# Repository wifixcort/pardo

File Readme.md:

Pardo Board

M0 personaliced. Based on Adafruit Feather M0

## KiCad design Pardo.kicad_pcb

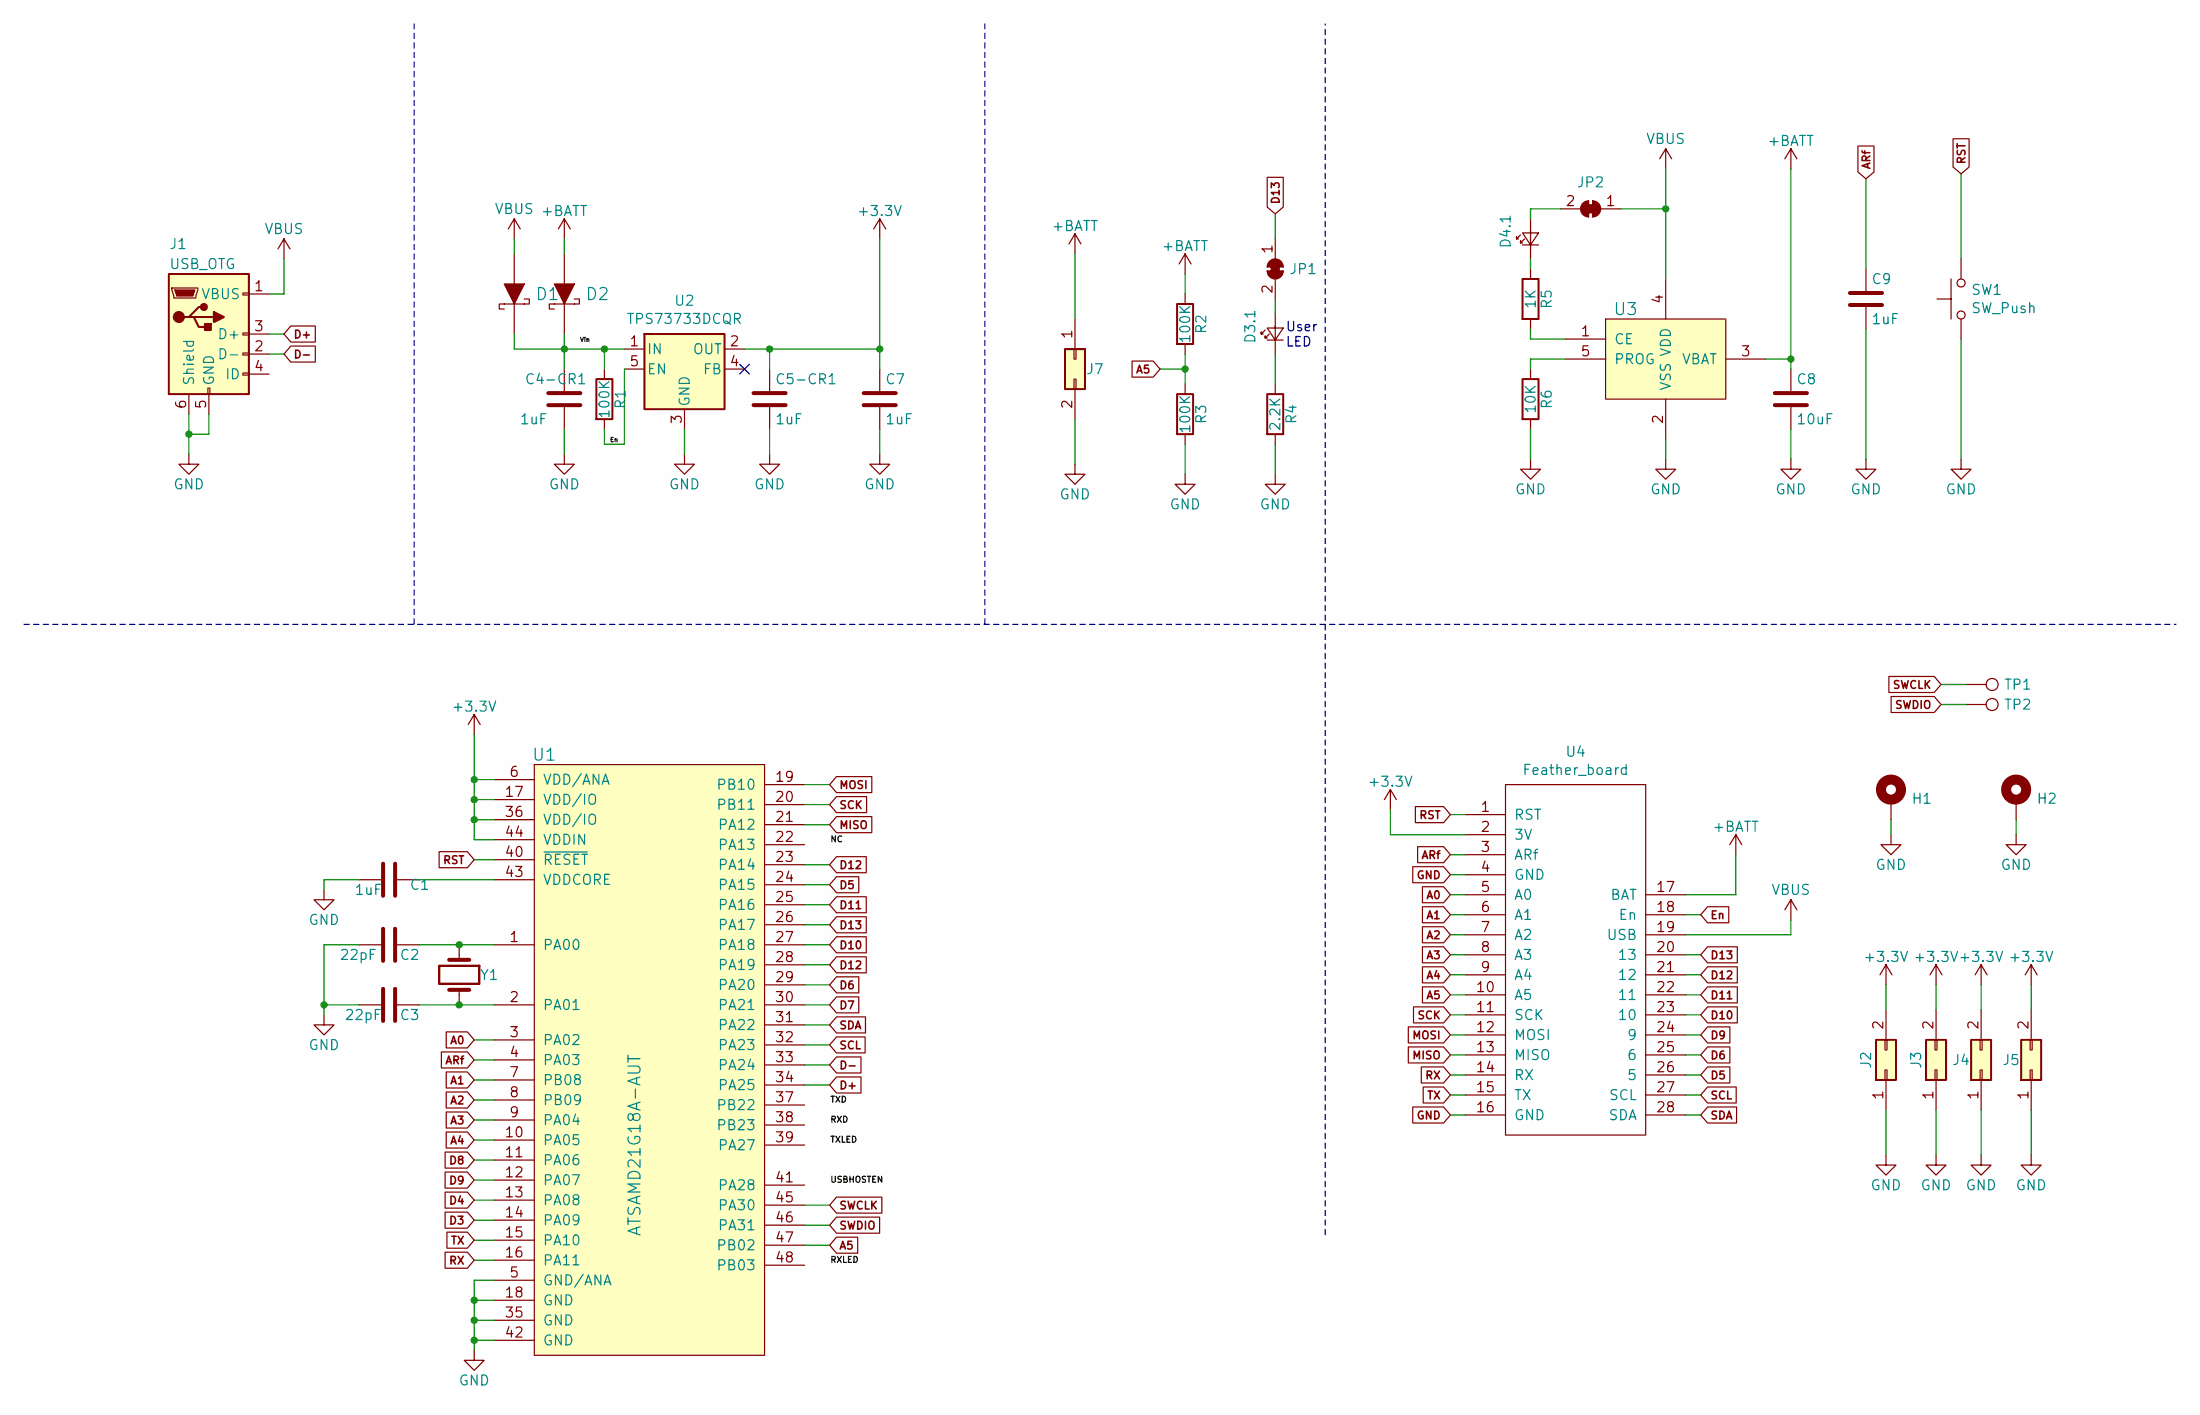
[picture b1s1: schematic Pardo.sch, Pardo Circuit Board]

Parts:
C1, C4-CR1, C5-CR1, C7, C9: 1uF; C_0805_2012Metric_Pad1.15x1.40mm_HandSolder
C2, C3: 22pF; C_0805_2012Metric_Pad1.15x1.40mm_HandSolder
C8: 10uF; C_0805_2012Metric_Pad1.15x1.40mm_HandSolder
D1, D2: MBR0520LT1G; SOD-123; MPN MBR0520LT1G; Digi-Key_PN MBR0520LT1GOSCT-ND
D3.1: D13; LED_0603_1608Metric_Pad1.05x0.95mm_HandSolder
D4.1: CHG; LED_0603_1608Metric_Pad1.05x0.95mm_HandSolder
H1, H2: MountingHole_Pad; MountingHole_2.2mm_M2_ISO7380_Pad
J1: USB_OTG; USB_Micro-B_Molex_47346-0001
J2, J3, J4, J5: Conn_02x01; PinHeader_1x02_P2.54mm_Vertical
J7: Conn_02x01; JST-2-SMD
JP1, JP2: SolderJumper_2_Bridged; SolderJumper-2_P1.3mm_Bridged_RoundedPad1.0x1.5mm
R1, R2, R3: 100K; R_0805_2012Metric_Pad1.15x1.40mm_HandSolder
R4: 2.2K; R_0805_2012Metric_Pad1.15x1.40mm_HandSolder
R5: 1K; R_0805_2012Metric_Pad1.15x1.40mm_HandSolder
R6: 10K; R_0805_2012Metric_Pad1.15x1.40mm_HandSolder
SW1: SW_Push; SW_SPST_B3U-1000P
TP1, TP2: TestPoint; TestPoint_THTPad_1.0x1.0mm_Drill0.5mm
U1: ATSAMD21G18A-AUT; TQFP-48_7x7mm; MPN ATSAMD21G18A-AUT; Digi-Key_PN ATSAMD21G18A-AUTCT-ND
U2: TPS73733DCQR; SOT-223-6_TabPin6
U3: MCP73832T-2ACI_OT; SOT-753; MPN MCP73832T-2ACI/OT; Digi-Key_PN MCP73832T-2ACI/OTCT-ND
U4: Feather_board; Feather Shield
Y1: Crystal; Crystal_SMD_3215-2Pin_3.2x1.5mm

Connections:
+3V3: C5-CR1.1, C7.1, J2.2, J3.2, J4.2, J5.2, U1.6 (VDD/ANA), U1.17 (VDD/IO), U1.36 (VDD/IO), U1.44 (VDDIN), U2.2 (OUT), U4.2 (3V)
+BATT: C8.1, D2.A, J7.1, R2.1, U3.3 (VBAT), U4.17 (BAT)
A0: U1.3 (PA02), U4.5 (A0)
A1: U1.7 (PB08), U4.6 (A1)
A2: U1.8 (PB09), U4.7 (A2)
A3: U1.9 (PA04), U4.8 (A3)
A4: U1.10 (PA05), U4.9 (A4)
A5: R2.2, R3.1, U1.47 (PB02), U4.10 (A5)
ARf: C9.1, U1.4 (PA03), U4.3 (ARf)
D3: U1.14 (PA09)
D4: U1.13 (PA08)
D5: U1.24 (PA15), U4.26 (5)
D6: U1.29 (PA20), U4.25 (6)
D7: U1.30 (PA21)
D8: U1.11 (PA06)
D9: U1.12 (PA07), U4.24 (9)
D10: U1.27 (PA18), U4.23 (10)
D11: U1.25 (PA16), U4.22 (11)
D12: U1.23 (PA14), U1.28 (PA19), U4.21 (12)
D13: JP1.1 (A), U1.26 (PA17), U4.20 (13)
D+: J1.3 (D+), U1.34 (PA25)
D-: J1.2 (D-), U1.33 (PA24)
En: R1.2, U2.5 (EN), U4.18 (En)
GND: C1.2, C2.2, C3.2, C4-CR1.2, C5-CR1.2, C7.2, C8.2, C9.2, H1.1, H2.1, J1.5 (GND), J1.6 (Shield), J2.1, J3.1, J4.1, J5.1, J7.2, R3.2, R4.2, R6.2, SW1.1, U1.5 (GND/ANA), U1.18 (GND), U1.35 (GND), U1.42 (GND), U2.3 (GND), U3.2 (VSS), U4.4 (GND), U4.16 (GND)
MISO: U1.21 (PA12), U4.13 (MISO)
MOSI: U1.19 (PB10), U4.12 (MOSI)
unnamed: C1.1, U1.43 (VDDCORE)
unnamed: C2.1, U1.1 (PA00), Y1.1
unnamed: C3.1, U1.2 (PA01), Y1.2
unnamed: C4-CR1.1, D1.K, D2.K, R1.1, U2.1 (IN)
unnamed: D3.1.1 (K), R4.1
unnamed: D3.1.2 (A), JP1.2 (B)
unnamed: D4.1.1 (K), R5.1
unnamed: D4.1.2 (A), JP2.2 (B)
unnamed: R5.2, U3.1 (CE)
unnamed: R6.1, U3.5 (PROG)
RST: SW1.2, U1.40 (~RESET), U4.1 (RST)
RX: U1.16 (PA11), U4.14 (RX)
SCK: U1.20 (PB11), U4.11 (SCK)
SCL: U1.32 (PA23), U4.27 (SCL)
SDA: U1.31 (PA22), U4.28 (SDA)
SWCLK: TP1.1, U1.45 (PA30)
SWDIO: TP2.1, U1.46 (PA31)
TX: U1.15 (PA10), U4.15 (TX)
VBUS: D1.A, J1.1 (VBUS), JP2.1 (A), U3.4 (VDD), U4.19 (USB)

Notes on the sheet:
User LED

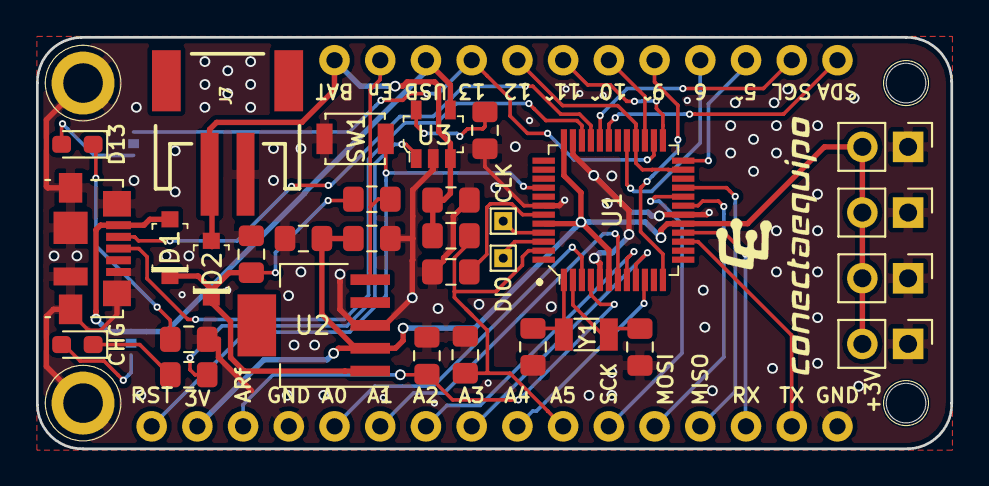
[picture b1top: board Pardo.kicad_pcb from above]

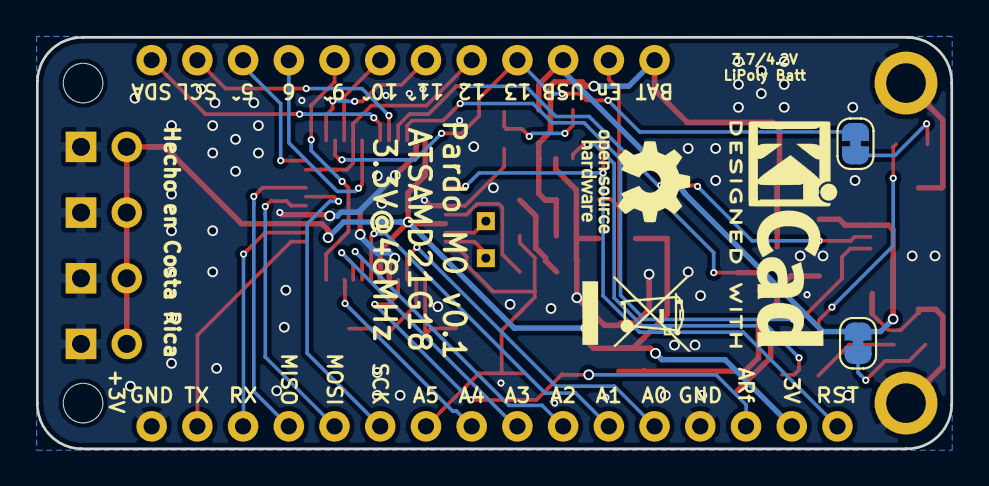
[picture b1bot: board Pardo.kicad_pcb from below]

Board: 2 copper layers, 50.8 x 22.9 mm, 36 parts (2 on the bottom side), 41 nets.

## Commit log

2020-08-20 Pardo version 0.1
2020-08-20 adding .gitignore
2020-08-20 Adding more bias
2020-08-23 minor updates
2020-08-23 D2 batt schk deleted
2020-08-23 D2 batt schk restore
2020-11-05 Pardo fab 1
2020-11-09 LICENSE & Readme
